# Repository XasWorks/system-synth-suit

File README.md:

# system-synth-suit
Repo collecting design files for the "System" Synth suit, from schematics to concepts to programs! Follow along and build your own suit along~!

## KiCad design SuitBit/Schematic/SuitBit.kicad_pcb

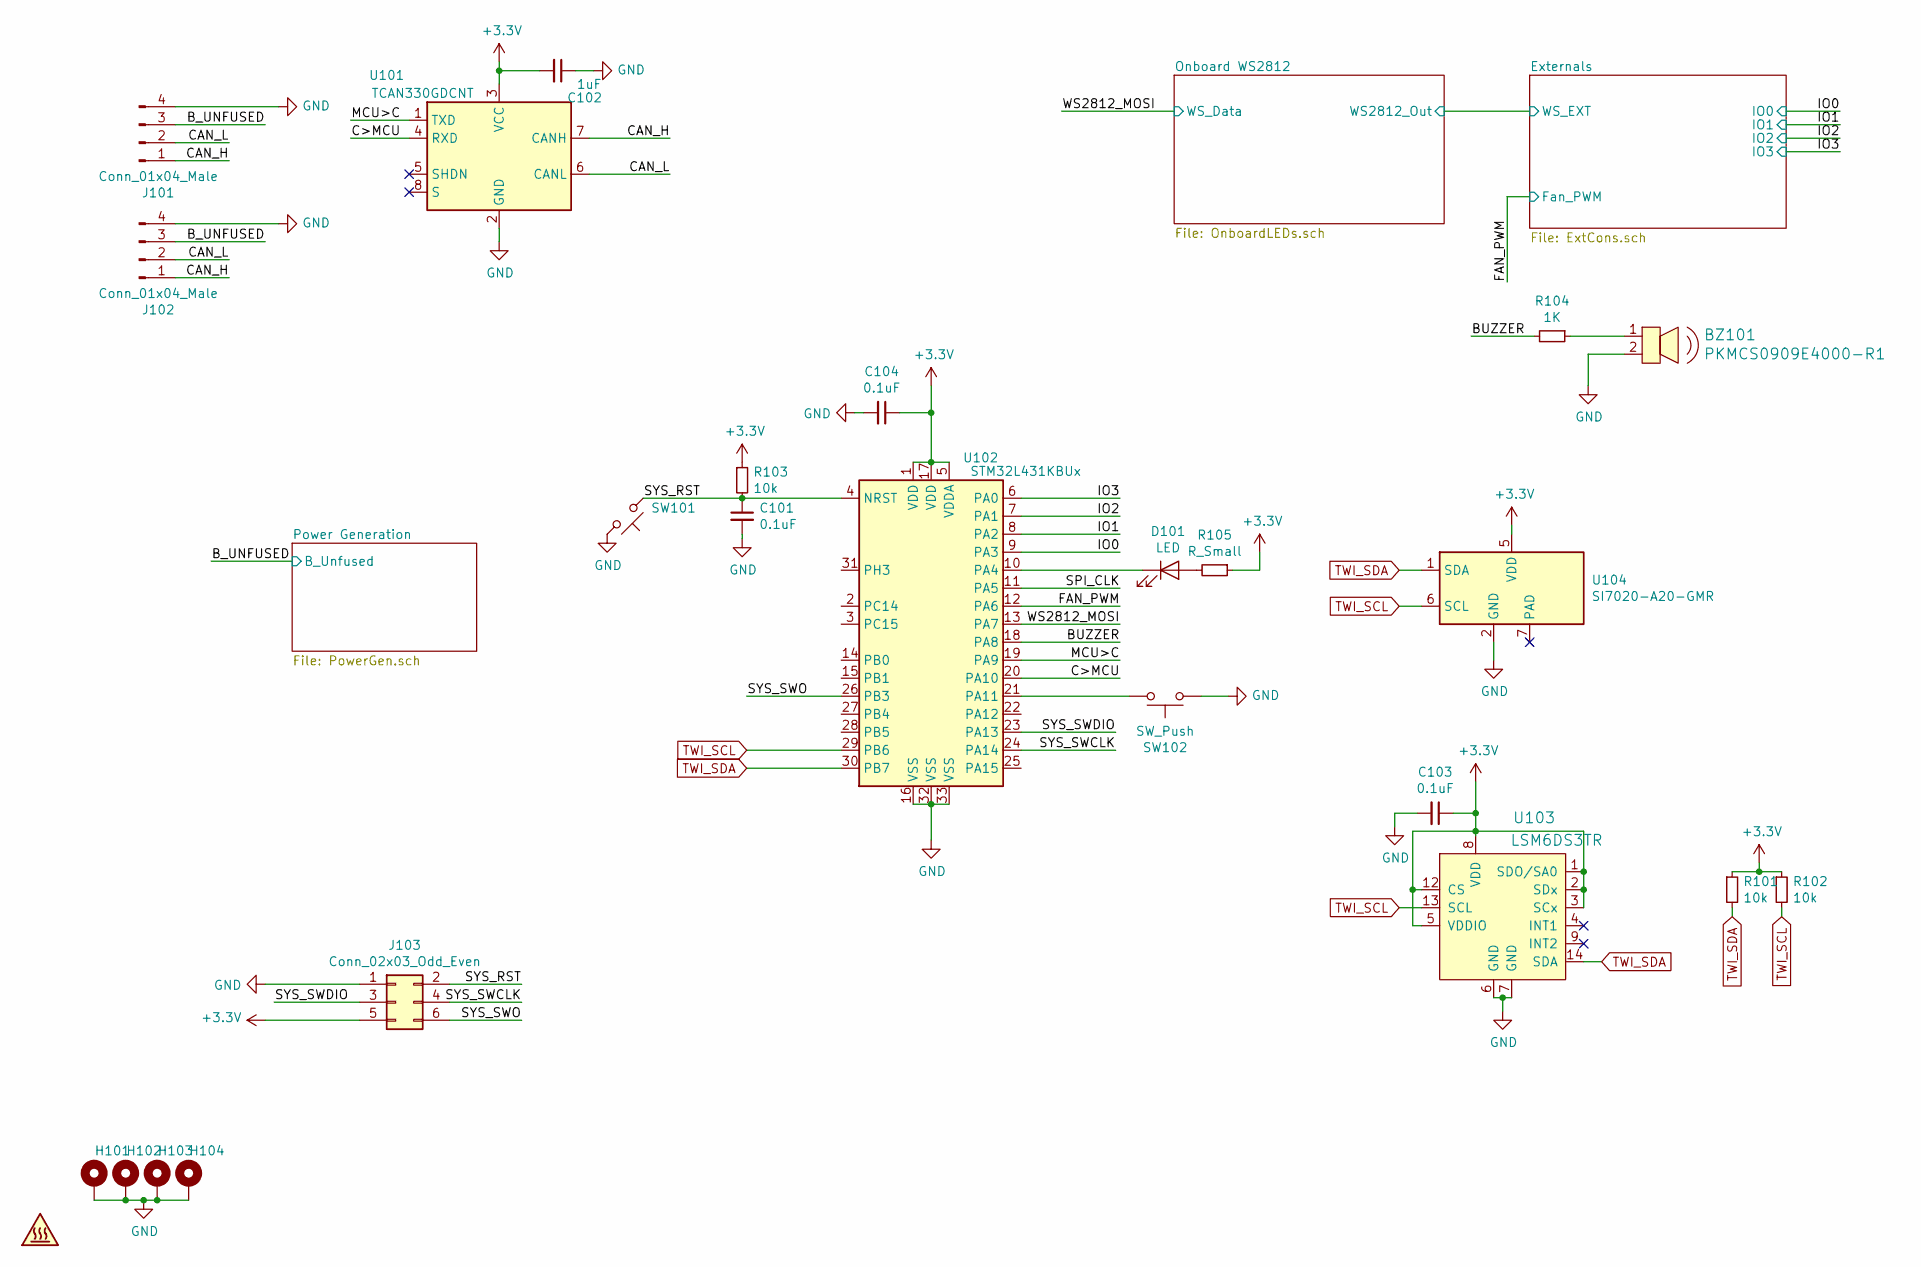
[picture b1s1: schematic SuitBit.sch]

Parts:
BZ101: PKMCS0909E4000-R1; Piezo_9x9mm_PKMCS0909E4000-R1; MPN PKMCS0909E4000-R1; Digi-Key_PN 490-9647-1-ND
C101, C103, C104: 0.1uF; C_0603_1608Metric
C102: 1uF; C_0805_2012Metric
D101: LED; LED_0603_1608Metric
H101, H102, H103, H104: MountingHole_Pad; MountingHole_2.2mm_M2_DIN965_Pad
J101, J102: Conn_01x04_Male; PinHeader_1x04_P2.54mm_Horizontal
J103: Conn_02x03_Odd_Even; PinHeader_2x03_P2.00mm_Vertical
R101, R102, R103: 10k; R_0603_1608Metric
R104: 1K; R_0603_1608Metric
R105: R_Small; R_0603_1608Metric
SW101: RS-282G05A3-SM RT; SW_SPST_CK_RS282G05A3
SW102: SW_Push; SW_SPST_PTS645
SYM101: SYM_Hot_Small; DragonIcon_25mm
U101: TCAN330GDCNT; SOT-23-8
U102: STM32L431KBUx; QFN-32-1EP_5x5mm_P0.5mm_EP3.45x3.45mm
U103: LSM6DS3TR; LGA-14L_2.5x3mm__LSM6DS3; MPN LSM6DS3TR; Digi-Key_PN 497-15383-1-ND
U104: SI7020-A20-GMR; DFN-6-1EP_3x3mm_P1mm_EP1.5x2.4mm

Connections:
+3V3: C102.2, C103.1, C104.1, J103.5, R101.1, R102.1, R103.1, R105.1, U101.3 (VCC), U102.1 (VDD), U102.5 (VDDA), U102.17 (VDD), U103.1 (SDO/SA0), U103.2 (SDx), U103.3 (SCx), U103.5 (VDDIO), U103.8 (VDD), U103.12 (CS), U104.5 (VDD); also elsewhere on the board
/BUZZER: R104.2, U102.18 (PA8)
/B_UNFUSED: J101.3, J102.3; also elsewhere on the board
/C>MCU: U101.4 (RXD), U102.20 (PA10)
/CAN_H: J101.1, J102.1, U101.7 (CANH)
/CAN_L: J101.2, J102.2, U101.6 (CANL)
/FAN_PWM: U102.12 (PA6); also elsewhere on the board
/IO0: U102.9 (PA3); also elsewhere on the board
/IO1: U102.8 (PA2); also elsewhere on the board
/IO2: U102.7 (PA1); also elsewhere on the board
/IO3: U102.6 (PA0); also elsewhere on the board
/MCU>C: U101.1 (TXD), U102.19 (PA9)
/SPI_CLK: U102.11 (PA5)
/SYS_RST: C101.1, J103.2, R103.2, SW101.1, U102.4 (NRST)
/SYS_SWCLK: J103.4, U102.24 (PA14)
/SYS_SWDIO: J103.3, U102.23 (PA13)
/SYS_SWO: J103.6, U102.26 (PB3)
/WS2812_MOSI: U102.13 (PA7); also elsewhere on the board
GND: BZ101.2, C101.2, C102.1, C103.2, C104.2, H101.1, H102.1, H103.1, H104.1, J101.4, J102.4, J103.1, SW101.2, SW102.1, U101.2 (GND), U102.16 (VSS), U102.32 (VSS), U102.33 (VSS), U103.6 (GND), U103.7 (GND), U104.2 (GND); also elsewhere on the board
unnamed: BZ101.1, R104.1
unnamed: D101.1 (K), U102.10 (PA4)
unnamed: D101.2 (A), R105.2
unnamed: SW102.2, U102.21 (PA11)
TWI_SCL: R102.2, U102.29 (PB6), U103.13 (SCL), U104.6 (SCL); also elsewhere on the board
TWI_SDA: R101.2, U102.30 (PB7), U103.14 (SDA), U104.1 (SDA); also elsewhere on the board

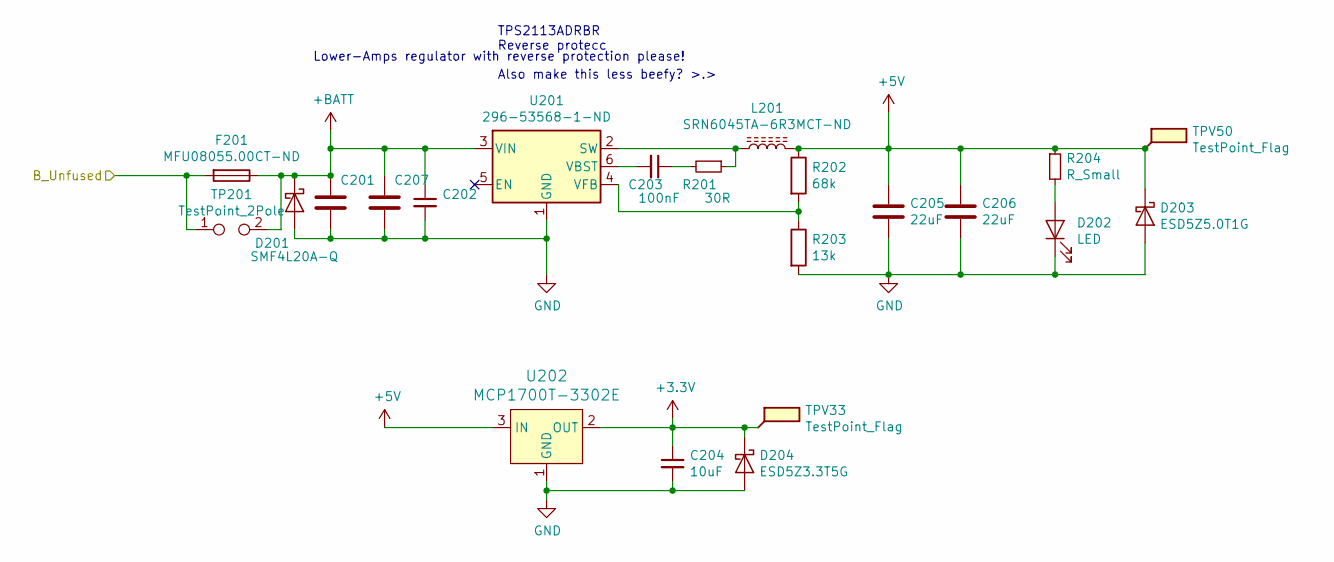
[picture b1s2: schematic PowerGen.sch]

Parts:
C201, C204, C207: 10uF; C_0805_2012Metric
C202: 399-7845-1-ND; C_0603_1608Metric
C203: 100nF; C_0603_1608Metric
C205: 22uF; C_0805_2012Metric; DigiKey 490-7611-1-ND
C206: 22uF; C_0805_2012Metric
D201: SMF4L20A-Q; D_SOD-123
D202: LED; LED_0603_1608Metric
D203: ESD5Z5.0T1G; D_SOD-523
D204: ESD5Z3.3T5G; D_SOD-523
F201: MFU08055.00CT-ND; Fuse_0805_2012Metric
L201: SRN6045TA-6R3MCT-ND; L_Bourns_SRN6045TA
R201: 30R; R_0603_1608Metric
R202: 68k; R_0603_1608Metric
R203: 13k; R_0603_1608Metric
R204: R_Small; R_0603_1608Metric
TP201: TestPoint_2Pole; TestPoint_2Pads_Pitch2.54mm_Drill0.8mm
TPV33, TPV50: TestPoint_Flag; TestPoint_Loop_D2.50mm_Drill1.0mm_LowProfile
U201: 296-53568-1-ND; SOT-23-6
U202: MCP1700T-3302E; SOT-23-3; MPN MCP1700T-3302E/TT; Digi-Key_PN MCP1700T3302ETTCT-ND

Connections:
+3V3: C204.1, D204.1 (K), TPV33.1, U202.2 (OUT); also elsewhere on the board
+5V: C205.1, C206.1, D203.1 (K), L201.2, R202.1, R204.1, TPV50.1, U202.3 (IN); also elsewhere on the board
+BATT: C201.1, C202.1, C207.1, D201.1 (K), F201.1, TP201.2, U201.3 (VIN)
/B_UNFUSED: F201.2, TP201.1; also elsewhere on the board
GND: C201.2, C202.2, C204.2, C205.2, C206.2, C207.2, D201.2 (A), D202.1 (K), D203.2 (A), D204.2 (A), R203.2, U201.1 (GND), U202.1 (GND); also elsewhere on the board
unnamed: C203.1, R201.2
unnamed: C203.2, U201.6 (VBST)
unnamed: D202.2 (A), R204.2
unnamed: L201.1, R201.1, U201.2 (SW)
unnamed: R202.2, R203.1, U201.4 (VFB)

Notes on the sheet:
TPS2113ADRBR Reverse protecc Also make this less beefy? >.>
Lower-Amps regulator with reverse protection please!

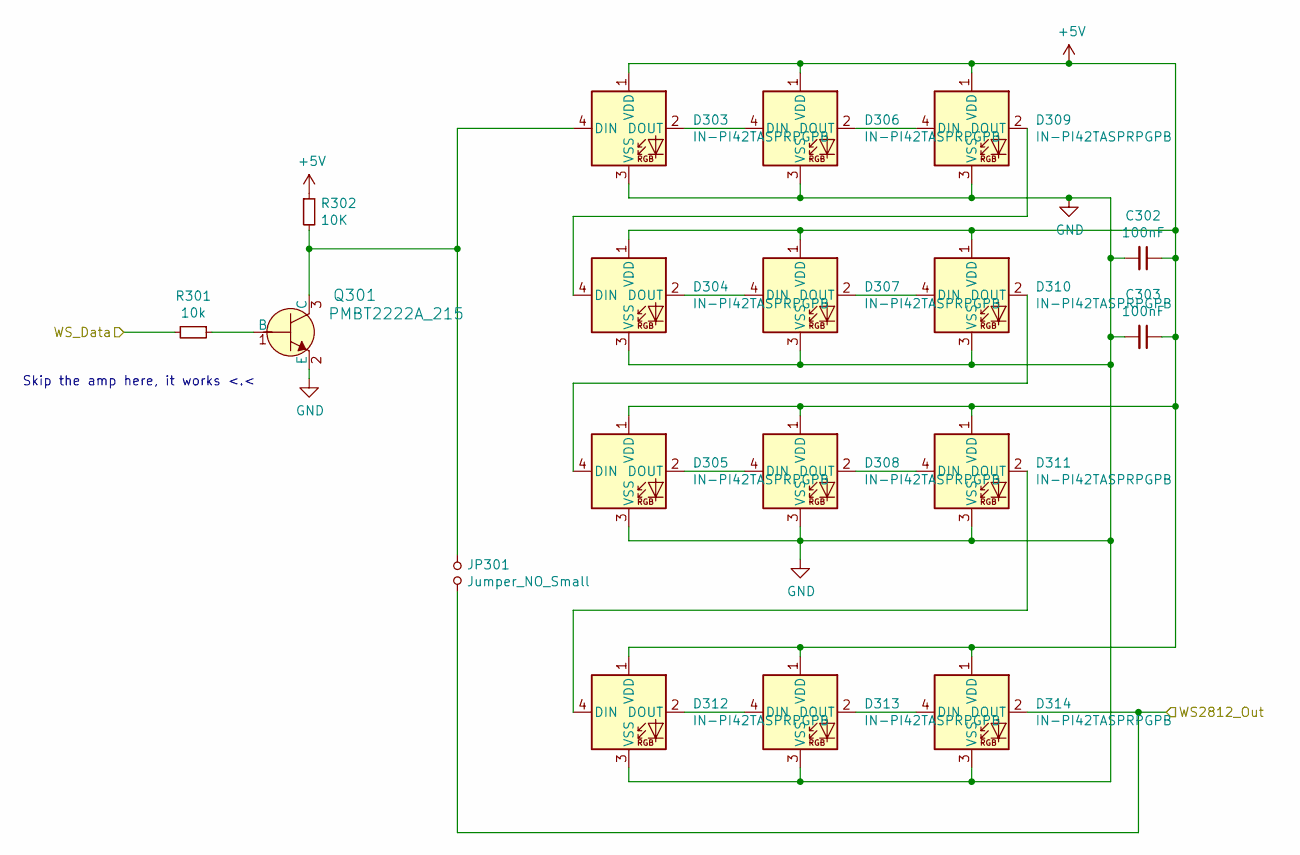
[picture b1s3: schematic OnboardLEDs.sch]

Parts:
C302, C303: 100nF; C_0603_1608Metric
D303, D304, D305, D306, D307, D308, D309, D310, D311, D312, D313, D314: IN-PI42TASPRPGPB; IN-PI42TAS
JP301: Jumper_NO_Small; SolderJumper-2_P1.3mm_Open_TrianglePad1.0x1.5mm
Q301: PMBT2222A_215; SOT-23-3; MPN PMBT2222A,215; Digi-Key_PN 1727-2956-1-ND
R301: 10k; R_0603_1608Metric
R302: 10K; R_0603_1608Metric

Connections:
+5V: C302.1, C303.1, D303.1 (VDD), D304.1 (VDD), D305.1 (VDD), D306.1 (VDD), D307.1 (VDD), D308.1 (VDD), D309.1 (VDD), D310.1 (VDD), D311.1 (VDD), D312.1 (VDD), D313.1 (VDD), D314.1 (VDD), R302.1; also elsewhere on the board
/Onboard WS2812/WS2812_Out: D314.2 (DOUT), JP301.2; also elsewhere on the board
/WS2812_MOSI: R301.2; also elsewhere on the board
GND: C302.2, C303.2, D303.3 (VSS), D304.3 (VSS), D305.3 (VSS), D306.3 (VSS), D307.3 (VSS), D308.3 (VSS), D309.3 (VSS), D310.3 (VSS), D311.3 (VSS), D312.3 (VSS), D313.3 (VSS), D314.3 (VSS), Q301.2 (E); also elsewhere on the board
unnamed: D303.2 (DOUT), D306.4 (DIN)
unnamed: D303.4 (DIN), JP301.1, Q301.3 (C), R302.2
unnamed: D304.2 (DOUT), D307.4 (DIN)
unnamed: D304.4 (DIN), D309.2 (DOUT)
unnamed: D305.2 (DOUT), D308.4 (DIN)
unnamed: D305.4 (DIN), D310.2 (DOUT)
unnamed: D306.2 (DOUT), D309.4 (DIN)
unnamed: D307.2 (DOUT), D310.4 (DIN)
unnamed: D308.2 (DOUT), D311.4 (DIN)
unnamed: D311.2 (DOUT), D312.4 (DIN)
unnamed: D312.2 (DOUT), D313.4 (DIN)
unnamed: D313.2 (DOUT), D314.4 (DIN)
unnamed: Q301.1 (B), R301.1

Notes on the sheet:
Skip the amp here, it works <.<

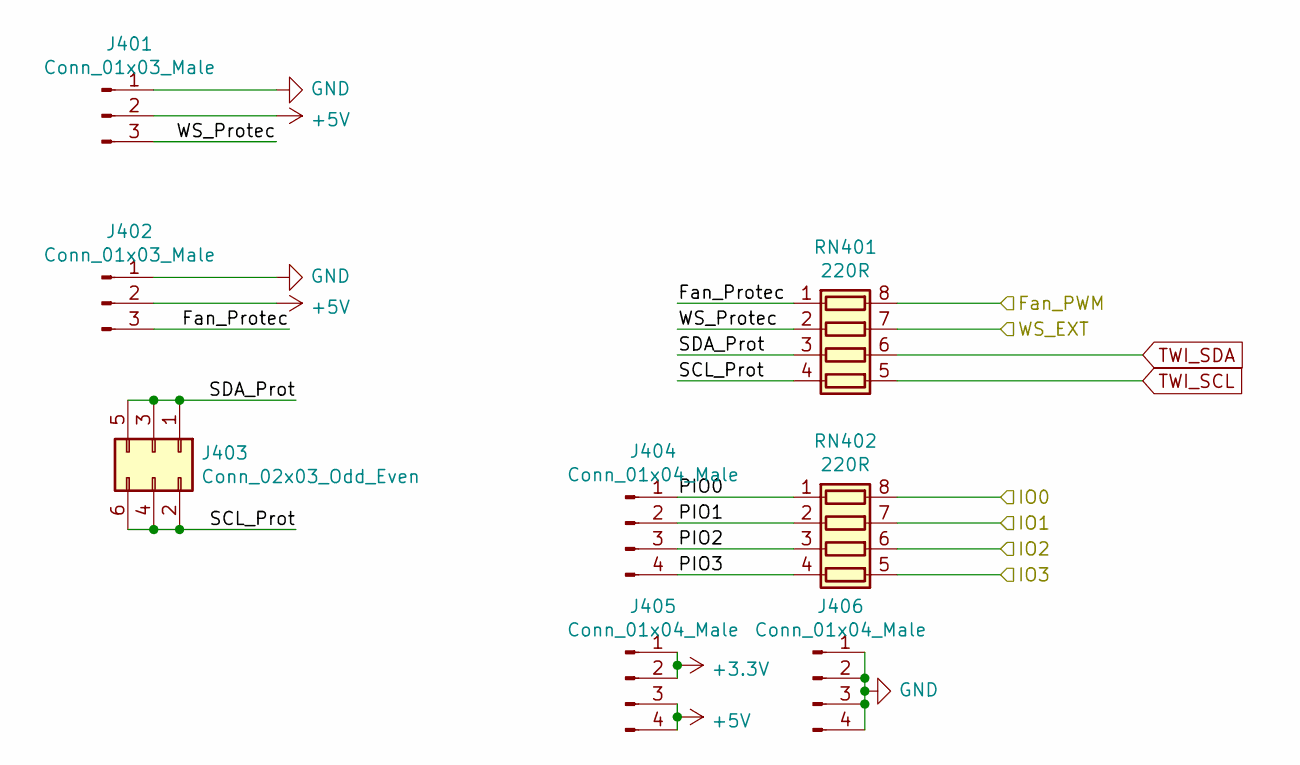
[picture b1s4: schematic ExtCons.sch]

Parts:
J401, J402: Conn_01x03_Male; PinHeader_1x03_P2.00mm_Vertical
J403: Conn_02x03_Odd_Even; PinHeader_2x03_P2.00mm_Vertical
J404, J405, J406: Conn_01x04_Male; PinHeader_1x04_P2.00mm_Vertical
RN401, RN402: 220R; R_Array_Convex_4x0603

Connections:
+3V3: J405.1, J405.2; also elsewhere on the board
+5V: J401.2, J402.2, J405.3, J405.4; also elsewhere on the board
/Externals/Fan_Protec: J402.3, RN401.1 (R1.1)
/Externals/PIO0: J404.1, RN402.1 (R1.1)
/Externals/PIO1: J404.2, RN402.2 (R2.1)
/Externals/PIO2: J404.3, RN402.3 (R3.1)
/Externals/PIO3: J404.4, RN402.4 (R4.1)
/Externals/SCL_Prot: J403.2, J403.4, J403.6, RN401.4 (R4.1)
/Externals/SDA_Prot: J403.1, J403.3, J403.5, RN401.3 (R3.1)
/Externals/WS_Protec: J401.3, RN401.2 (R2.1)
/FAN_PWM: RN401.8 (R1.2); also elsewhere on the board
/IO0: RN402.8 (R1.2); also elsewhere on the board
/IO1: RN402.7 (R2.2); also elsewhere on the board
/IO2: RN402.6 (R3.2); also elsewhere on the board
/IO3: RN402.5 (R4.2); also elsewhere on the board
/Onboard WS2812/WS2812_Out: RN401.7 (R2.2); also elsewhere on the board
GND: J401.1, J402.1, J406.1, J406.2, J406.3, J406.4; also elsewhere on the board
TWI_SCL: RN401.5 (R4.2); also elsewhere on the board
TWI_SDA: RN401.6 (R3.2); also elsewhere on the board

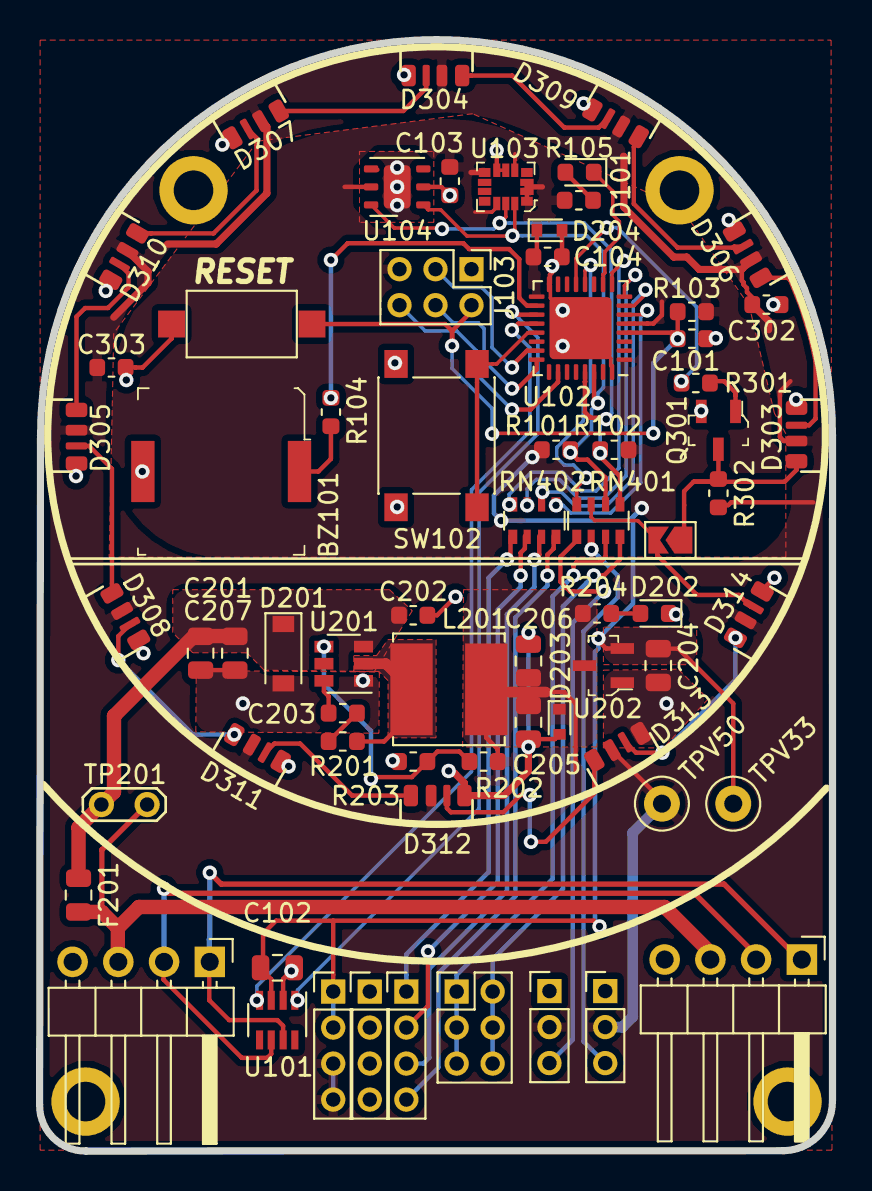
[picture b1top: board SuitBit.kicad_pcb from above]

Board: 2 copper layers, 44.1 x 61.7 mm, 73 parts (1 on the bottom side), 53 nets.

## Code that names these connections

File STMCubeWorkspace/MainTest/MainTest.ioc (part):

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Mcu.Name=STM32L431K(B-C)Ux
Mcu.Package=UFQFPN32
Mcu.UserName=STM32L431KBUx
PA0.Signal=GPIO_Analog
PA1.Signal=GPIO_Analog
PA10.Mode=Asynchronous
PA10.Signal=USART1_RX
PA11.GPIOParameters=GPIO_PuPd,GPIO_Label
PA11.GPIO_Label=BTN_INT
PA11.GPIO_PuPd=GPIO_PULLUP
PA11.Signal=GPIO_Input
PA2.Signal=GPIO_Analog
PA3.Signal=GPIO_Analog
PA4.GPIOParameters=GPIO_Label
PA4.GPIO_Label=PIN_LED
PA4.Signal=GPIO_Output
PA5.Mode=TX_Only_Simplex_Unidirect_Master
PA5.Signal=SPI1_SCK
PA6.Signal=S_TIM16_CH1
PA7.Mode=TX_Only_Simplex_Unidirect_Master
PA7.Signal=SPI1_MOSI
PA8.Signal=S_TIM1_CH1
PA9.Mode=Asynchronous
PA9.Signal=USART1_TX
PB3\ (JTDO-TRACESWO).Signal=GPIO_Output
PB6.Mode=I2C
PB6.Signal=I2C1_SCL
PB7.Mode=I2C
PB7.Signal=I2C1_SDA
RCC.HSE_VALUE=8000000
RCC.SYSCLKFreq_VALUE=80000000
RCC.SYSCLKSource=RCC_SYSCLKSOURCE_PLLCLK
board=custom

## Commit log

2020-01-04 Begin work on the SuitBit!
2020-01-17 Moar work on the suit bit
2020-01-27 Continue power work
2020-02-02 Add a local XasCode submodule
2020-02-03 More tweaking
2020-02-03 Added lib table
2020-02-03 Moved folders a little
2020-02-05 Continued work on the PCB I think
2020-02-06 Began work on som routing
2020-02-06 Begin implementation of the STM chip
2020-02-06 Add the STM Cube IDE workspace
2020-02-12 Tweak CubeIDE s'more
2020-02-12 Add a new 'playground ' This will allow us to experiment with CMU Sphinx and voice effects a bit more
    ;
2020-02-12 Continue work on the SuitBit
2020-02-12 Update XasCode a bit
2020-02-14 Continue work on the Synth Hardware
2020-02-14 Work a tid bit more on the electronics
2020-02-14 Add startrek sounds and kill switch
2020-02-19 Continue work on the PCB
2020-02-19 New footprint, yay
2020-02-20 Preliminarily finish routing
2020-02-20 Add a new project for 32-pin MCU
2020-02-27 Work, quite a bit more, on the STM code
2020-02-27 Finalize the PCB a bit
2020-02-27 Smol audio tweaks
2020-03-15 Set up main workspace with first LED test
2020-03-15 Update XasCode
2020-03-15 Implement actually useful Gitignore
2020-03-17 Play s'more with the glow
2020-03-21 PERFECTLY BALANCED
2020-04-15 Add FurComs module
2020-05-08 Update subprojects
2020-05-08 Adjust STMCube settings (eh)
2020-05-08 ... Look, it works We know this happens. Things pile up, I forgot what does what why, but it still works <.<
2020-05-08 Move VoiceControl test to better location
2020-05-08 Add a Ruby-Based animation and sequencing control
2020-05-08 Add a few more STMCube changes
2020-05-08 Perform a few more small tweaks
2020-05-14 Perform small cleanups
2020-05-14 Add YAML-Based saving of sound silences
    This massively improves startup time because... Well, we don't have to
    wait for silence generation each time <.<
2020-05-14 Add a "Parameter Stack"
    It allows easy and seamless overwriting of a wide range of config
    values, which is useful in order to stack animations, reuse components,
    and provide a more unified interface.
    Any "global" option like speech, colour palette, etc., shall run over
    this.
2020-05-14 Move the speech recognition to a separate thread
    Reduces lag in the time-sensitive main processing thread, uses system
    resources a bit better etc.
2020-05-14 Use new parameter stack, forward audio, use FurComs etc.
2020-05-14 Adjust sheets to use new Parameter Stack
2020-05-14 Add FurComs TX on button press/depress
2020-05-16 Add generic 'configure' function to simplify shape init
2020-05-16 Remove unused old test file
2020-05-16 Add delete when new value is set to nil
    This makes it very easy to relinquish control of a certain variable
2020-05-16 Add length of audio detection
    This will always ensure a properly sorted hash with beginning and end
    keys
2020-05-16 Adjust the generic speech pattern
2020-05-19 Remove now obsolte music file
2020-05-19 Add sheet-internal music playback
    Sheets can now play and kill music easily; playing music will be killed
    when the sheet is torn down
2020-05-19 Use the new sheet internal music playback
2020-05-19 Add sequence key to opts
    This way, flexible multi-key sheets can react to which key was used
2020-05-19 Add a Red/Blue/Black alert ambiance
2020-05-19 Add the new eyes class to C++
2020-05-19 Implement and play with the eyes in Ruby
2020-05-19 Stage updated XasCode
2020-05-19 Gitignore Control.JSGF
2020-05-19 Move Ruby code to submodule and adjust c++ project
2020-05-19 Update and use new submodule Ruby libs
2020-06-08 Add proper mem management from nadler (again)
2020-06-08 Add a STM32F7xx workspace to test LED panel driving
2020-06-08 Play around with the ruby a bit more!
2020-06-08 Update submodules a bit
2020-06-08 Add moved sound files
2020-06-20 Swap tef-hub75 with tef-led-magic
    The new repo will contain both the SPI NeoPixel handler code, as well as
    the Hub75 code and generic colour handling.
    That way it's a bit more compact.
2020-06-27 Remove some annoying/glitchy code
2020-06-27 Add CoreTest UART Files and try out FurComs
2020-06-27 Remove now unused XasCode module
2020-06-27 Use new Matrix and LED code
2020-06-27 Change a few settings for test animations
2020-07-24 Improve test startup procedure
2020-07-24 Module bump
2020-07-24 Add a few extra LEDs to the glove
2020-07-28 Added attempted head model
2020-08-23 Add blender files for the head
